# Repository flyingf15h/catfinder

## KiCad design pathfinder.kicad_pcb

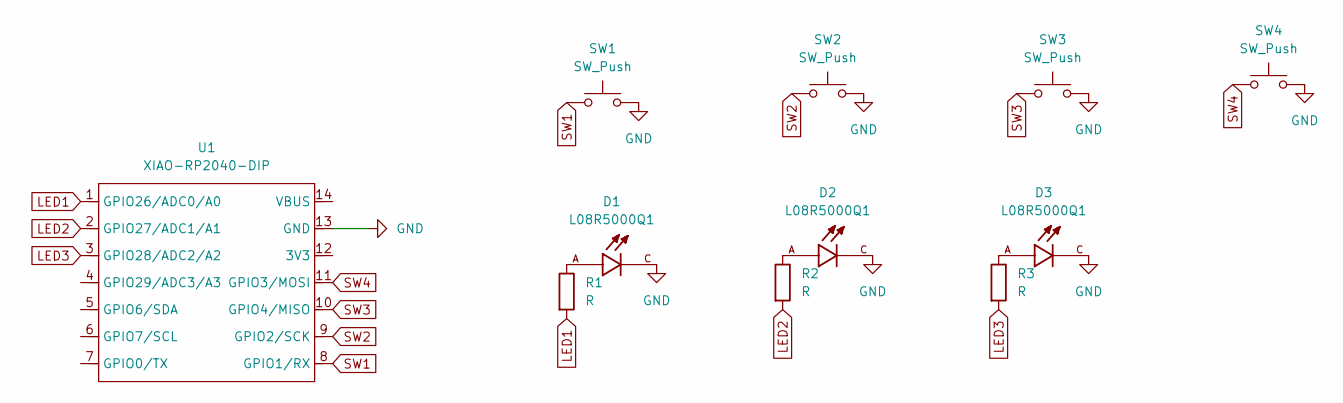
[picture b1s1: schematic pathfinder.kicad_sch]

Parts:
D1, D2, D3: L08R5000Q1; LEDRD254W57D500H1070; PARTREV NA
R1, R2, R3: R; R_Axial_DIN0204_L3.6mm_D1.6mm_P5.08mm_Horizontal
SW1, SW2, SW3, SW4: SW_Push; SW_Cherry_MX_1.00u_PCB
U1: XIAO-RP2040-DIP

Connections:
GND: D1.C, D2.C, D3.C, SW1.2, SW2.2, SW3.2, SW4.2, U1.13 (GND)
LED1: R1.2, U1.1 (GPIO26/ADC0/A0)
LED2: R2.2, U1.2 (GPIO27/ADC1/A1)
LED3: R3.2, U1.3 (GPIO28/ADC2/A2)
unnamed: D1.A, R1.1
unnamed: D2.A, R2.1
unnamed: D3.A, R3.1
SW1: SW1.1, U1.8 (GPIO1/RX)
SW2: SW2.1, U1.9 (GPIO2/SCK)
SW3: SW3.1, U1.10 (GPIO4/MISO)
SW4: SW4.1, U1.11 (GPIO3/MOSI)

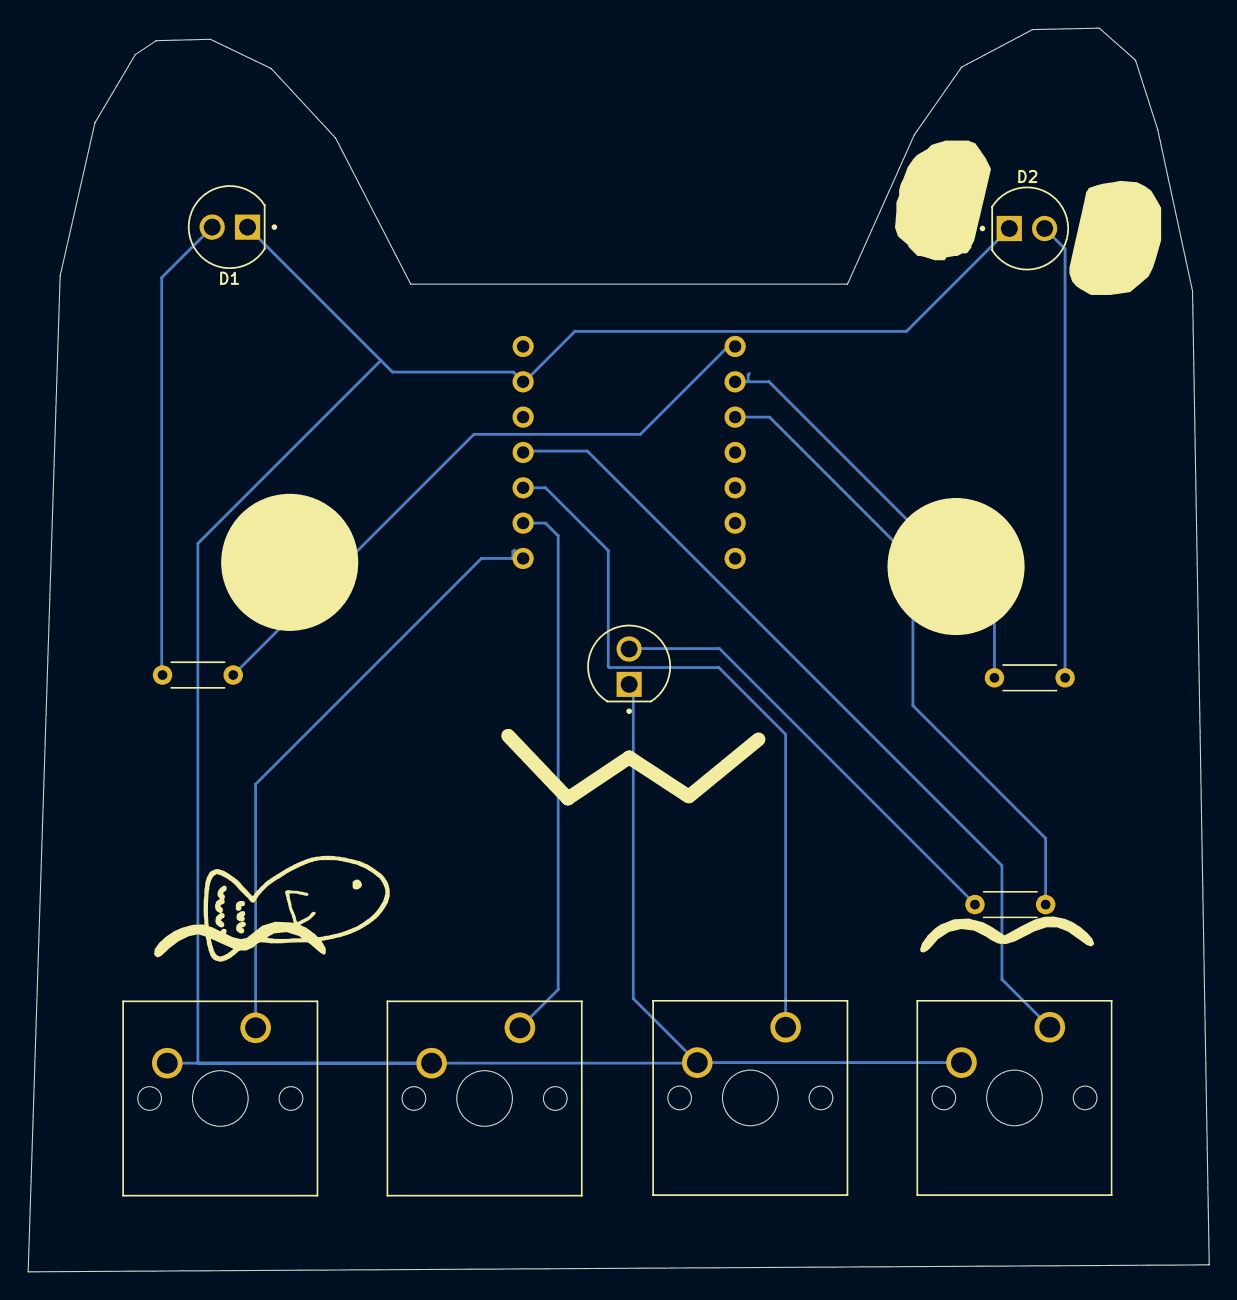
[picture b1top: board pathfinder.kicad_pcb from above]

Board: 2 copper layers, 84.9 x 89.4 mm, 11 parts (1 on the bottom side), 11 nets.
